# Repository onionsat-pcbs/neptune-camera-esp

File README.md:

# Neptune Camera ESP
PCB for project neptune

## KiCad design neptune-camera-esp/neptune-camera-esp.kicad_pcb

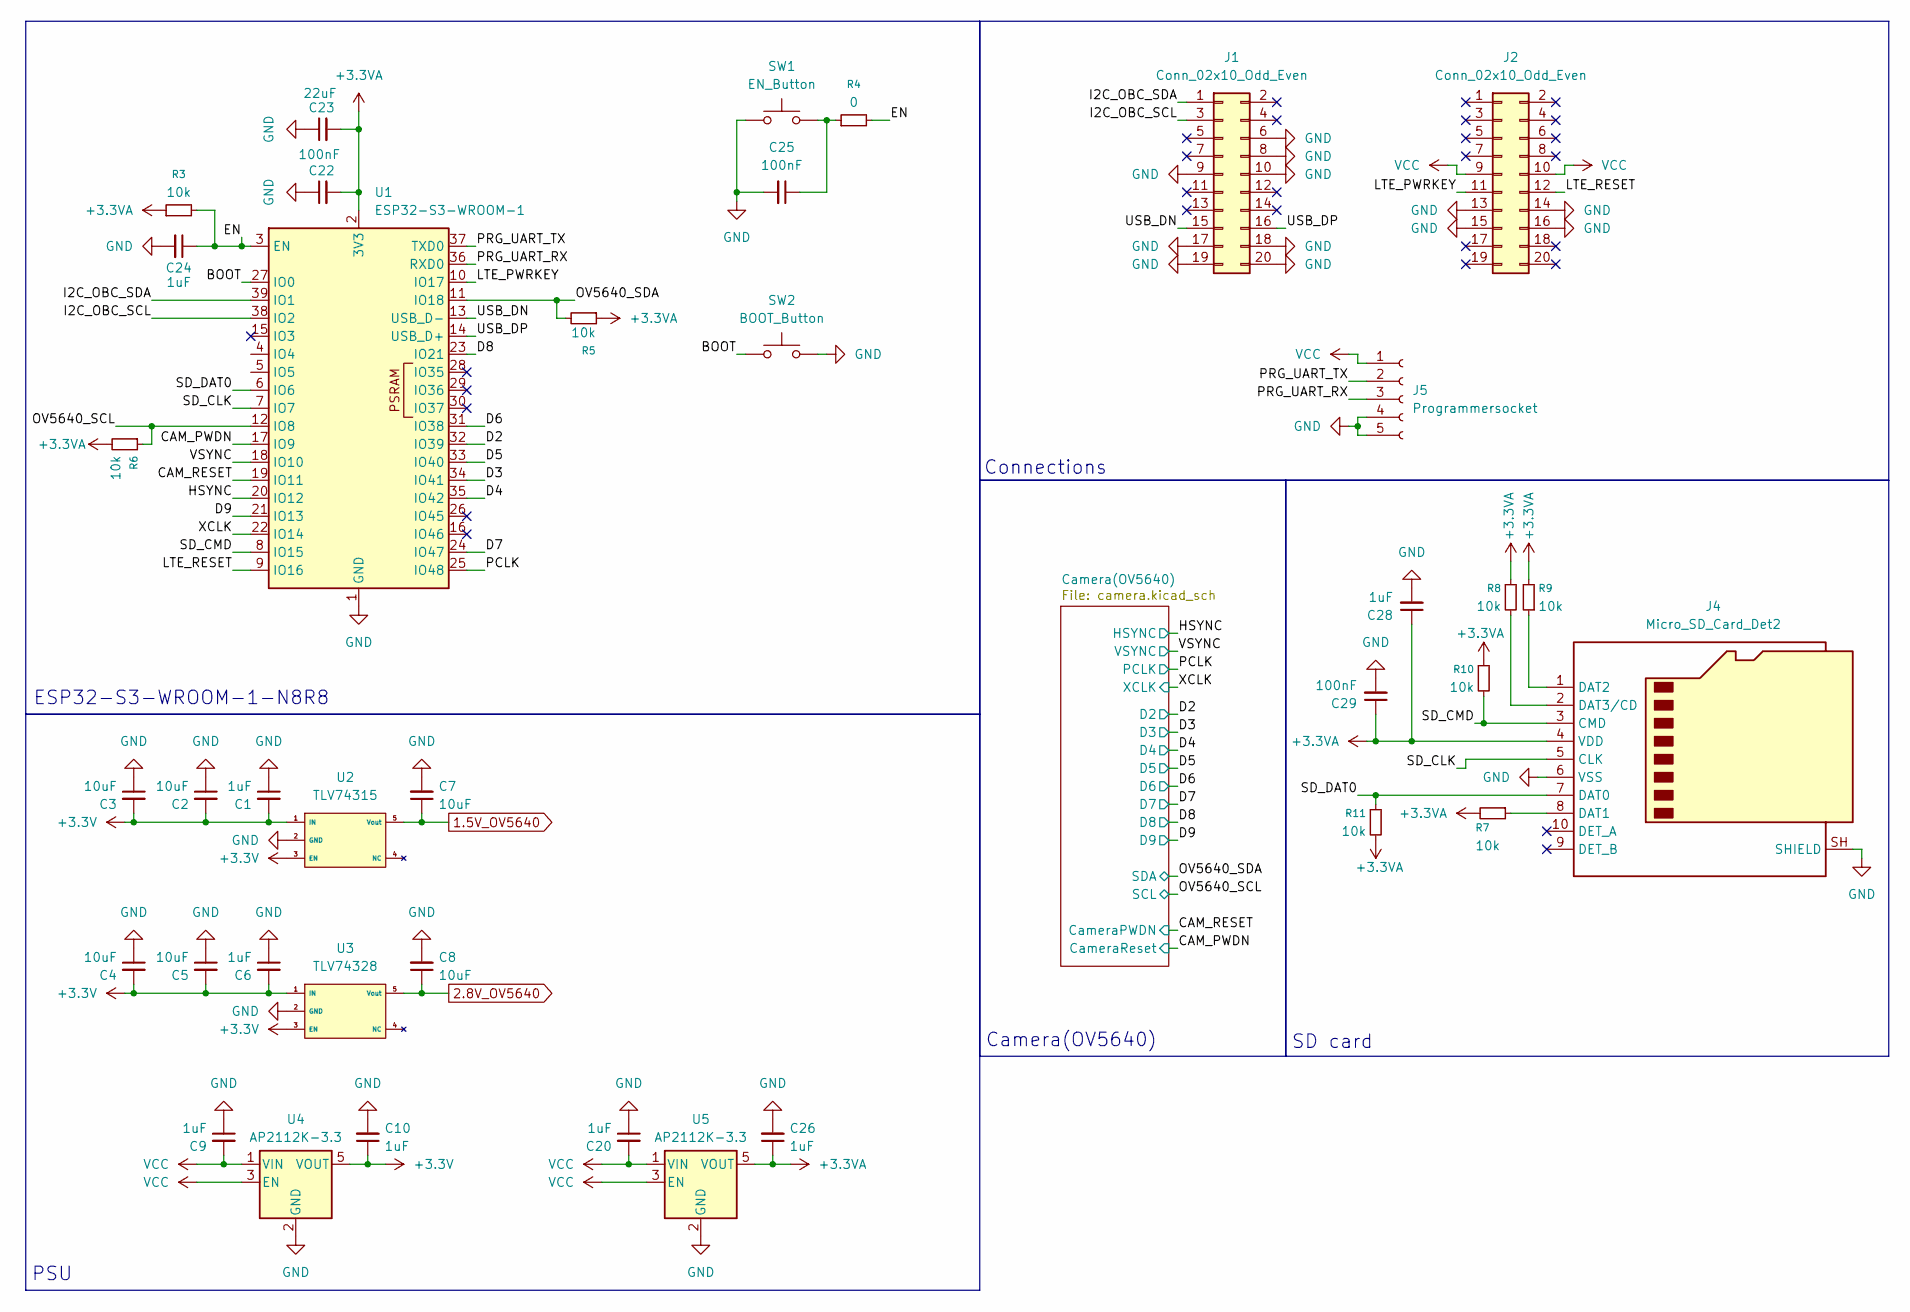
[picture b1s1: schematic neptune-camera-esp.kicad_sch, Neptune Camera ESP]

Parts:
C1, C6, C9, C10, C20, C26, C28: 1uF; C_0603_1608Metric
C2, C3, C4, C5, C7, C8: 10uF; C_0603_1608Metric
C22, C25: 100nF; C_0603_1608Metric
C23: 22uF; C_0805_2012Metric
C24: 1uF; C_0402_1005Metric
C29: 100nF; C_0402_1005Metric
J1, J2: Conn_02x10_Odd_Even; PinHeader_2x10_P2.00mm_Vertical_SMD
J4: Micro_SD_Card_Det2; microSD_HC_Hirose_DM3D-SF
J5: Programmersocket; PinSocket_1x05_P2.54mm_Horizontal
R3, R5, R6, R7, R8, R9, R10, R11: 10k; R_0402_1005Metric
R4: 0; R_0402_1005Metric
SW1: EN_Button; KEY-SMD_L4.0-W3.0-LS4.9-1
SW2: BOOT_Button; KEY-SMD_L4.0-W3.0-LS4.9-1
U1: ESP32-S3-WROOM-1; ESP32-S3-WROOM-1U
U2: TLV74315; SOT-23-5
U3: TLV74328; SOT-23-5
U4, U5: AP2112K-3.3; SOT-23-5

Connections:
1.5V_OV5640: C7.1, U2.5 (Vout); also elsewhere on the board
2.8V_OV5640: C8.1, U3.5 (Vout); also elsewhere on the board
+3.3V: C1.2, C2.2, C3.2, C4.2, C5.2, C6.2, C10.1, U2.1 (IN), U2.3 (EN), U3.1 (IN), U3.3 (EN), U4.5 (VOUT); also elsewhere on the board
+3.3VA: C22.2, C23.2, C26.1, C28.1, C29.1, J4.4 (VDD), R3.1, R5.1, R6.2, R7.2, R8.1, R9.2, R10.1, R11.2, U1.2 (3V3), U5.5 (VOUT); also elsewhere on the board
/BOOT: SW2.1, U1.27 (IO0)
/CAM_PWDN: U1.17 (IO9); also elsewhere on the board
/CAM_RESET: U1.19 (IO11); also elsewhere on the board
/D2: U1.32 (IO39); also elsewhere on the board
/D3: U1.34 (IO41); also elsewhere on the board
/D4: U1.35 (IO42); also elsewhere on the board
/D5: U1.33 (IO40); also elsewhere on the board
/D6: U1.31 (IO38); also elsewhere on the board
/D7: U1.24 (IO47); also elsewhere on the board
/D8: U1.23 (IO21); also elsewhere on the board
/D9: U1.21 (IO13); also elsewhere on the board
/EN: C24.1, R3.2, R4.2, U1.3 (EN)
/HSYNC: U1.20 (IO12); also elsewhere on the board
/I2C_OBC_SCL: J1.3, U1.38 (IO2)
/I2C_OBC_SDA: J1.1, U1.39 (IO1)
/LTE_PWRKEY: J2.11, U1.10 (IO17)
/LTE_RESET: J2.12, U1.9 (IO16)
/OV5640_SCL: R6.1, U1.12 (IO8); also elsewhere on the board
/OV5640_SDA: R5.2, U1.11 (IO18); also elsewhere on the board
/PCLK: U1.25 (IO48); also elsewhere on the board
/PRG_UART_RX: J5.3, U1.36 (RXD0)
/PRG_UART_TX: J5.2, U1.37 (TXD0)
/SD_CLK: J4.5 (CLK), U1.7 (IO7)
/SD_CMD: J4.3 (CMD), R10.2, U1.8 (IO15)
/SD_DAT0: J4.7 (DAT0), R11.1, U1.6 (IO6)
/USB_DN: J1.15, U1.13 (USB_D-)
/USB_DP: J1.16, U1.14 (USB_D+)
/VSYNC: U1.18 (IO10); also elsewhere on the board
/XCLK: U1.22 (IO14); also elsewhere on the board
GND: C1.1, C2.1, C3.1, C4.1, C5.1, C6.1, C7.2, C8.2, C9.1, C10.2, C20.1, C22.1, C23.1, C24.2, C25.2, C26.2, C28.2, C29.2, J1.6, J1.8, J1.9, J1.10, J1.17, J1.18, J1.19, J1.20, J2.13, J2.14, J2.15, J2.16, J4.6 (VSS), J4.SH (SHIELD), J5.4, J5.5, SW1.1, SW2.2, U1.1 (GND), U1.40 (GND), U1.41 (GND), U2.2 (GND), U3.2 (GND), U4.2 (GND), U5.2 (GND); also elsewhere on the board
unnamed: C25.1, R4.1, SW1.2
unnamed: J4.8 (DAT1), R7.1
unnamed: J4.1 (DAT2), R9.1
unnamed: J4.2 (DAT3/CD), R8.2
VCC: C9.2, C20.2, J2.9, J2.10, J5.1, U4.1 (VIN), U4.3 (EN), U5.1 (VIN), U5.3 (EN)

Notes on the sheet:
Connections
Camera(OV5640)
PSU
SD card
ESP32-S3-WROOM-1-N8R8

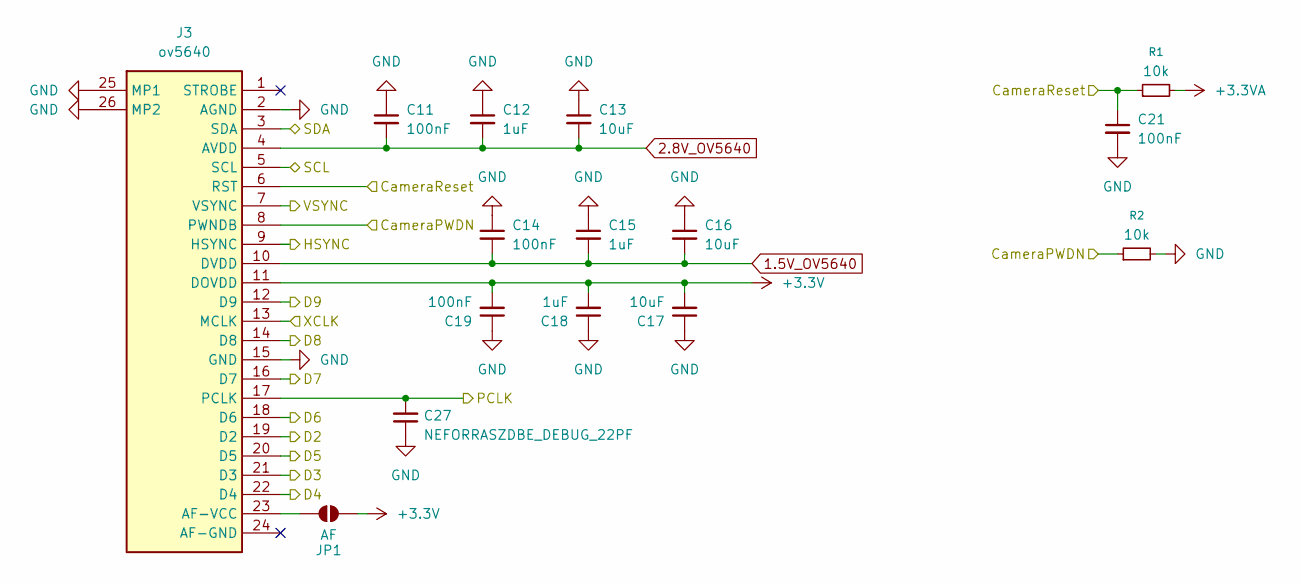
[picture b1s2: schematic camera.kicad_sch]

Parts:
C11, C14, C19, C21: 100nF; C_0402_1005Metric
C12, C15, C18: 1uF; C_0603_1608Metric
C13, C16, C17: 10uF; C_0603_1608Metric
C27: NEFORRASZDBE_DEBUG_22PF; C_0402_1005Metric
J3: ov5640; F33Z1A7Q1E8C24; Manufacturer_Part_Number F33Z-1A7Q1-E8C24
JP1: AF; SolderJumper-2_P1.3mm_Open_RoundedPad1.0x1.5mm
R1, R2: 10k; R_0402_1005Metric

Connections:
1.5V_OV5640: C14.2, C15.2, C16.2, J3.10 (DVDD); also elsewhere on the board
2.8V_OV5640: C11.2, C12.2, C13.2, J3.4 (AVDD); also elsewhere on the board
+3.3V: C17.2, C18.2, C19.2, J3.11 (DOVDD), JP1.1 (A); also elsewhere on the board
+3.3VA: R1.2; also elsewhere on the board
/CAM_PWDN: C21.1, J3.6 (RST), R1.1; also elsewhere on the board
/CAM_RESET: J3.8 (PWNDB), R2.1; also elsewhere on the board
/D2: J3.19 (D2); also elsewhere on the board
/D3: J3.21 (D3); also elsewhere on the board
/D4: J3.22 (D4); also elsewhere on the board
/D5: J3.20 (D5); also elsewhere on the board
/D6: J3.18 (D6); also elsewhere on the board
/D7: J3.16 (D7); also elsewhere on the board
/D8: J3.14 (D8); also elsewhere on the board
/D9: J3.12 (D9); also elsewhere on the board
/HSYNC: J3.9 (HSYNC); also elsewhere on the board
/OV5640_SCL: J3.5 (SCL); also elsewhere on the board
/OV5640_SDA: J3.3 (SDA); also elsewhere on the board
/PCLK: C27.2, J3.17 (PCLK); also elsewhere on the board
/VSYNC: J3.7 (VSYNC); also elsewhere on the board
/XCLK: J3.13 (MCLK); also elsewhere on the board
GND: C11.1, C12.1, C13.1, C14.1, C15.1, C16.1, C17.1, C18.1, C19.1, C21.2, C27.1, J3.2 (AGND), J3.15 (GND), J3.25 (MP1), J3.26 (MP2), R2.2; also elsewhere on the board
unnamed: J3.23 (AF-VCC), JP1.2 (B)

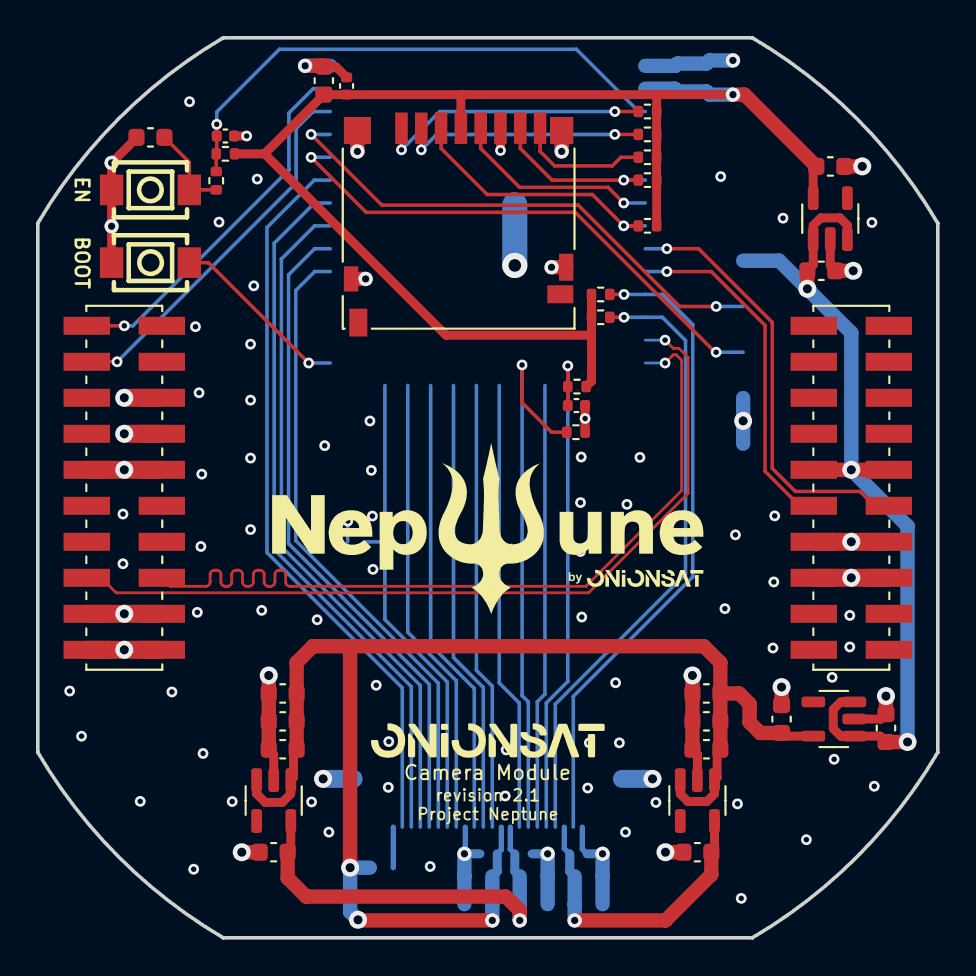
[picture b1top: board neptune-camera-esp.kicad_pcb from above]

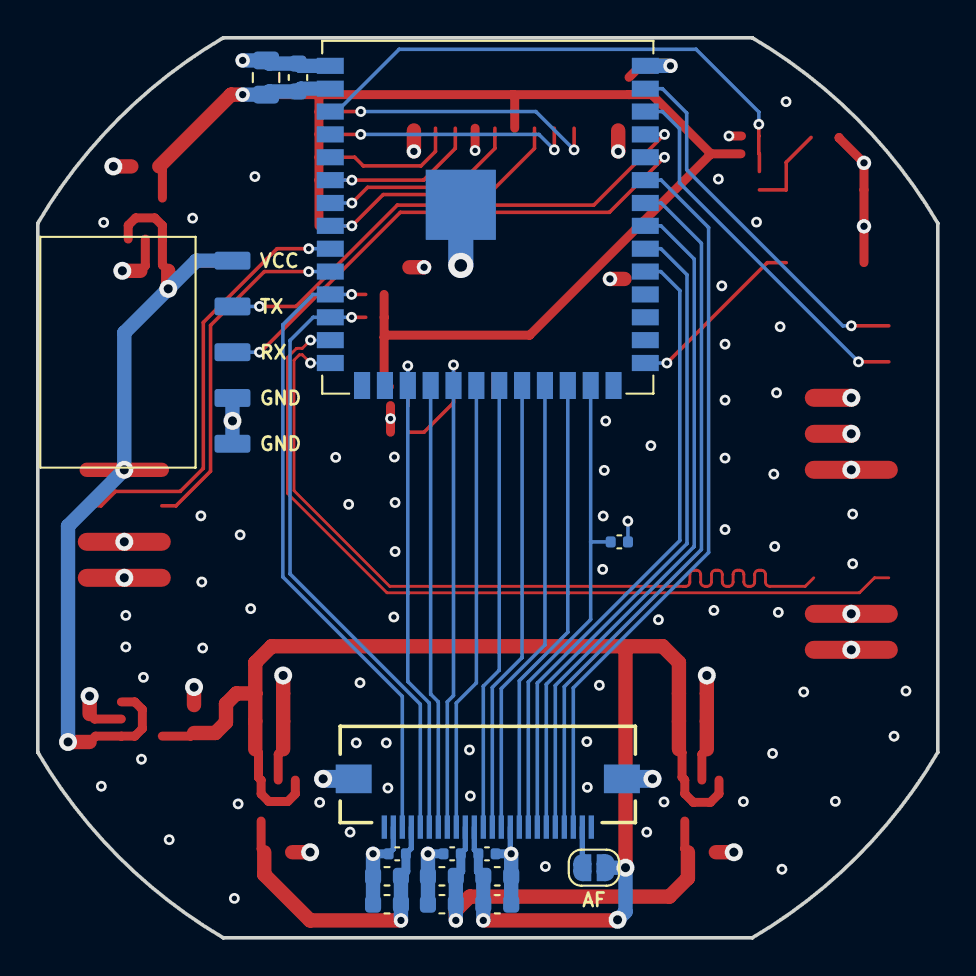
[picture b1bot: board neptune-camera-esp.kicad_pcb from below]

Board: 4 copper layers, 50.0 x 50.0 mm, 53 parts (16 on the bottom side), 40 nets.

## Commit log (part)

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2026-03-19 Fix project name capitalization in README
    Correct the capitalization of the project name in the README.
2026-03-19 inital relase
2026-03-19 Production
